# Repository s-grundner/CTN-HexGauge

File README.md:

# (EN) Hex Gauge

Customizable Automotive Gauge with CAN Bus and Integrated Inertial Measurement Unit

This is one of the initial Car Telemetry Networking (CTN) Projects.

The goal is to establish a Network of IoT devices for automotive telemtry capturing.

## Latest Revision

| Components Side | Display Side |
|-|-|
|||

## Repository Structure

- [Documentation](/documentation/)
- [Manufacturing](/manufacturing/)
- [Simulations](/simulations/)
- [Source Code](/source/)

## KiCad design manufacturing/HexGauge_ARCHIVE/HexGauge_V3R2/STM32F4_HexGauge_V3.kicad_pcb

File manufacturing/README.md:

# Revision 0

| Components Side | Display Side |
|-|-|
|||

Features:

- SD Card with SPI Mode
- IMU on I2C3 SMBA
- TFT on SPI1

# Revision 1

| Components Side | Display Side |
|-|-|
|||

Changes:

- Fullspeed SDIO Interface
- IMU on I2C1 SMBA
- Optimized Buck Converter
- Slope Control for CAN Bus
- 10pin Header for Debugging
- Larger Silkscreen
- JLC Tooling Holes

# Revision 2

| Components Side | Display Side |
|-|-|
|||

Changes:

- Simple Switcher Buckconverter Update
- Optimized Traces for
  - IMU
  - SD Card
  - SWD Interface
  - TFT Display
- Reduced Overall costs

# Revision 3

> In Development

Changes:

- [x] SD Card Dataline Pullups
- [x] change Stack-Up -> Sig/Pwr, GND, GND, Sig/Pwr
- [x] Buck converter Thinner Feedback Trace

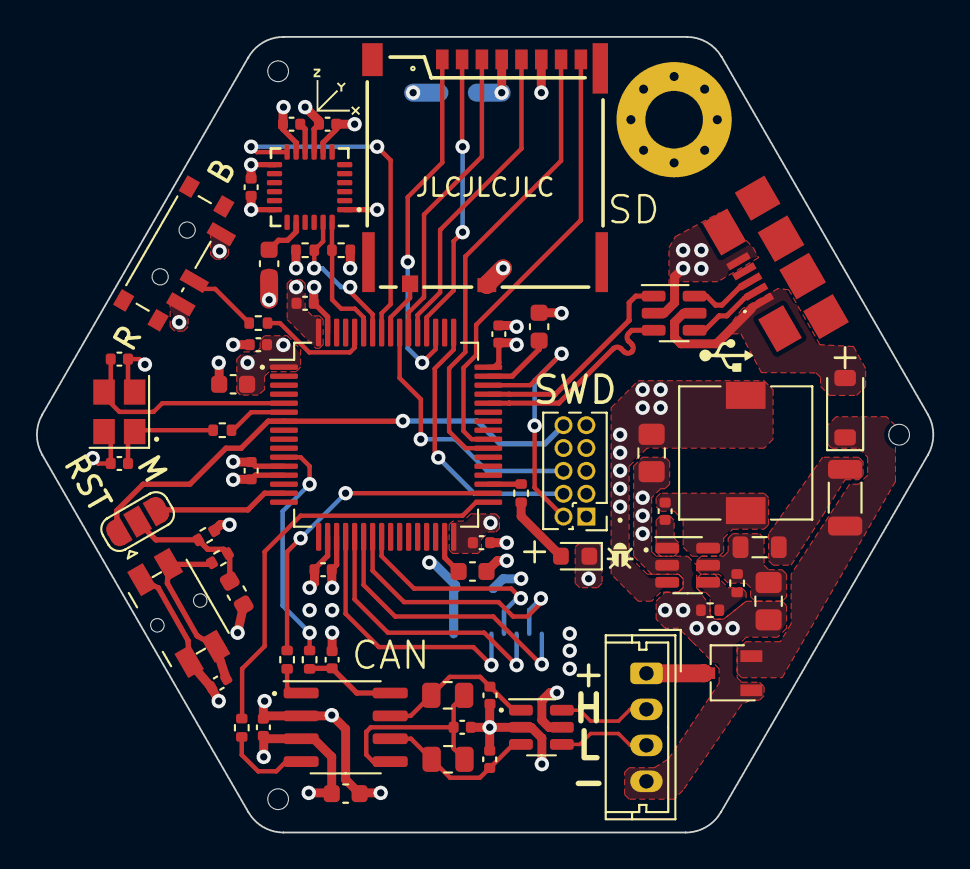
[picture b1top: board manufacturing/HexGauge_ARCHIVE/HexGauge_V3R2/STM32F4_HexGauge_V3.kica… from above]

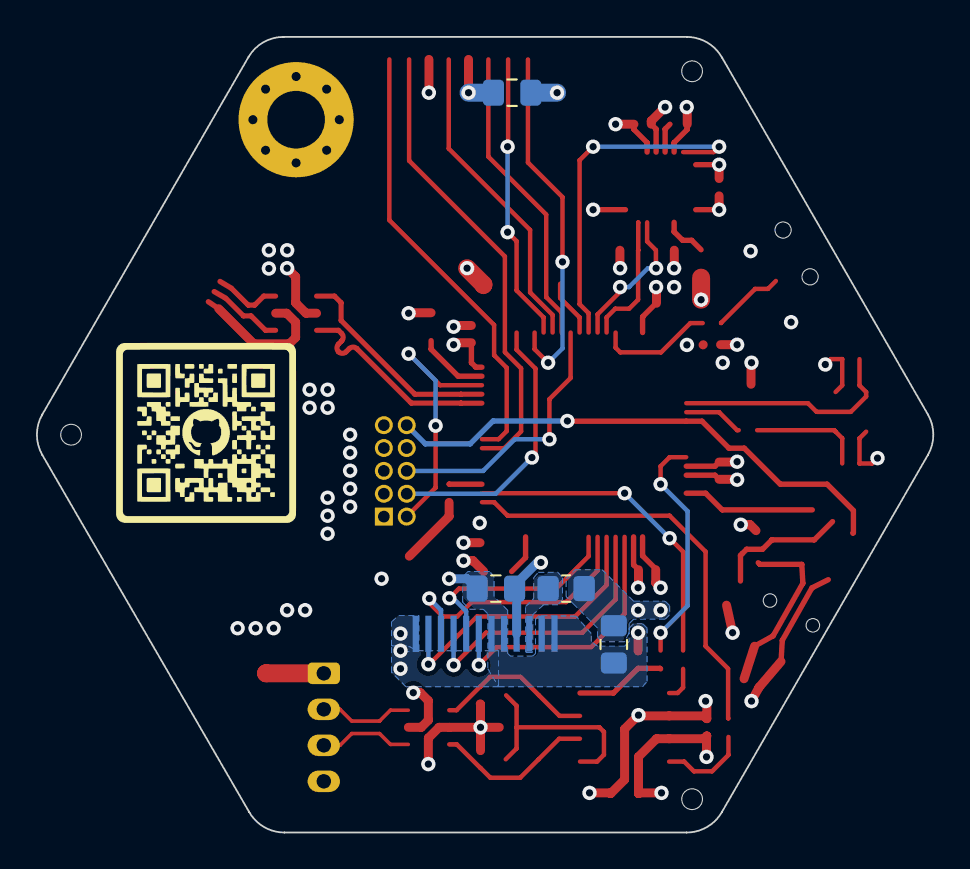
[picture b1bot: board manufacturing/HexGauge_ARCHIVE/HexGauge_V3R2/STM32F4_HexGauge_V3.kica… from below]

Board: 4 copper layers, 49.8 x 44.2 mm, 69 parts (5 on the bottom side), 59 nets.

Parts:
C1, C8, C12, C13, C17, C26: 2u2; C_0603_1608Metric
C2, C3, C4, C5, C6, C7, C9, C16, C18, C20, C21, C22, C23, C24, C25: 100n; C_0402_1005Metric
C10, C11: 12p; C_0402_1005Metric
C14, C29: 2u2; C_0805_2012Metric_Pad1.18x1.45mm_HandSolder
C15: 10u; C_0805_2012Metric_Pad1.18x1.45mm_HandSolder
C19: 10n; C_0402_1005Metric
C27, C28: 100n; C_0805_2012Metric_Pad1.18x1.45mm_HandSolder
D1: White; LED_0603_1608Metric
D2: B5819W; D_SOD-123
F1: 1A; L_1206_3216Metric
FB1: 100 @ 100MHz; L_0805_2012Metric
H1: ER_TFT128-1
H2: MountingHole; MountingHole_3.2mm_M3_Pad_Via
H3, H4, H5: JLC_Tooling
J1: USB_B_Micro; 101181920002LF
J3: Micro_SD_Card; 503398-1892
J4: Conn_01x04_Pin; Molex_Micro-Latch_53253-0470_1x04_P2.00mm_Vertical
J5: Conn_02x05_Odd_Even; PinHeader_2x05_P1.27mm_Vertical
JP1: Jumper_3_Bridged12; SolderJumper-3_P1.3mm_Open_RoundedPad1.0x1.5mm
L1: 3u3; L_7.3x7.3_H4.5
Q1: Q_PMOS_GSD; TSOT-23
R1: 10k; R_0402_1005Metric
R2, R3: 10R; R_0402_1005Metric
R4, R12, R14: 47R; R_0402_1005Metric
R5, R6, R7: 1k5; R_0402_1005Metric
R10, R16, R18: 100k; R_0402_1005Metric
R13, R15: 56R; R_0805_2012Metric
R17: 10R; R_0805_2012Metric_Pad1.20x1.40mm_HandSolder
SW1: SW_Panasonic_EVQPUC; Panasonic_EVQPUL_EVQPUC
SW2: SW_SPDT; SW_SPDT_PCM12
U1: STM32F405RGT6; LQFP-64_10x10mm_P0.5mm
U2: LMR16006YQ3; SOT-23-6
U3: SN65HVD230; SOIC-8_3.9x4.9mm_P1.27mm
U4, U6: USBLC6-2; SOT-23-6
U5: MPU-6050; InvenSense_QFN-24_4x4mm_P0.5mm
Y1: 25MHz 12pF; Crystal_SMD_3225-4Pin_3.2x2.5mm

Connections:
+3V3: C1.1, C2.1, C3.1, C4.1, C5.1, C6.1, C7.1, C15.1, C17.1, C18.1, C19.1, C20.1, C27.1, C28.1, C29.1, H1.4 (VDD), J3.4 (VDD), J5.1, L1.2, R1.1, R6.2, R7.2, R17.1, SW2.1 (A), U1.1 (VBAT), U1.13 (VDDA), U1.19 (VDD), U1.32 (VDD), U1.48 (VDD), U1.64 (VDD), U2.3 (FB), U3.3 (VCC), U4.5, U5.8 (VLOGIC), U5.13 (VDD)
+12V: J4.1, Q1.3 (D)
/Connectors/D+: J1.3 (D+), U6.6
/Connectors/D-: J1.2 (D-), U6.4
/Connectors/TFT_LEDA: H1.3 (LEDA), R17.2
/MCU/BOOT0: R2.2, U1.60 (BOOT0)
/MCU/DEBUG_LED: R5.2, U1.35 (PB14)
/MCU/HSE_IN: C10.1, U1.5 (PH0), Y1.3
/MCU/HSE_OUT: R4.2, U1.6 (PH1)
/MCU/VCAP_1: C12.1, U1.31 (VCAP_1)
/MCU/VCAP_2: C13.1, U1.47 (VCAP_2)
/MCU/XTAL_IN: C11.1, R4.1, Y1.1
/PMU/BUCK_BST: C16.1, U2.1 (CB)
/PMU/BUCK_EN: R10.2, R18.1, U2.4 (~SHDN)
/PMU/BUCK_IN: C14.1, FB1.2, R10.1, U2.5 (VIN)
/PMU/BUCK_OUT: C16.2, L1.1, U2.6 (SW)
/PMU/POST_FUSE: F1.2, FB1.1
/PMU/POST_POL: D2.1 (K), F1.1, Q1.2 (S)
/Sensors/CAN+: C21.1, R13.2, U3.7 (CANH), U4.1
/Sensors/CAN-: C23.2, R15.1, U3.6 (CANL), U4.3
/Sensors/CAN_RS: C24.1, R16.2, U3.8 (Rs)
/Sensors/VREF: C22.1, R13.1, R15.2, U3.5 (Vref)
BTN: JP1.3 (B), U1.15 (PA1)
CAN_CONN+: J4.2, U4.6
CAN_CONN-: J4.3, U4.4
CAN_RX: R14.1, U1.33 (PB12)
CAN_SC: R16.1, U1.11 (PC3)
CAN_TX: R12.1, U1.34 (PB13)
GND: C1.2, C2.2, C3.2, C4.2, C5.2, C6.2, C7.2, C8.2, C9.2, C10.2, C11.2, C12.2, C13.2, C14.2, C15.2, C17.2, C18.2, C19.2, C20.2, C21.2, C22.2, C23.1, C24.2, C25.2, C26.2, C27.2, C28.2, C29.2, D1.1 (K), H1.1 (GND), H1.2 (LEDK), H1.5 (GND), H1.6 (GND), H1.12 (GND), J1.5 (GND), J3.6 (VSS), J3.10 (SHIELD), J4.4, J5.3, J5.5, J5.9, Q1.1 (G), R18.2, SW1.1, SW2.3 (C), U1.12 (VSSA), U1.18 (VSS), U1.63 (VSS), U2.2 (GND), U3.2 (GND), U4.2, U5.1 (CLKIN), U5.9 (AD0), U5.11 (FSYNC), U5.18 (GND), U6.2, Y1.2, Y1.4
IMU_INT: U1.57 (PB5), U5.12 (INT)
IMU_SCL: R6.1, U1.58 (PB6), U5.23 (SCL)
IMU_SDA: R7.1, U1.59 (PB7), U5.24 (SDA)
NRST: J5.10, JP1.1 (A), U1.7 (NRST)
unnamed: C9.1, R3.2, SW1.2
unnamed: D1.2 (A), R5.1
unnamed: C8.1, JP1.2 (C), R1.2, R3.1
unnamed: R2.1, SW2.2 (B)
unnamed: R12.2, U3.1 (D)
unnamed: R14.2, U3.4 (R)
unnamed: C26.1, U5.20 (CPOUT)
unnamed: C25.1, U5.10 (REGOUT)
SD_CLK: J3.5 (CLK), U1.53 (PC12)
SD_CMD: J3.3 (CMD), U1.54 (PD2)
SD_DAT0: J3.7 (DAT0), U1.39 (PC8)
SD_DAT1: J3.8 (DAT1), U1.40 (PC9)
SD_DAT2: J3.1 (DAT2), U1.51 (PC10)
SD_DAT3: J3.2 (DAT3/CD), U1.52 (PC11)
SD_DET: J3.9 (DET), U1.56 (PB4)
SWCLK: J5.4, U1.49 (PA14)
SWDIO: J5.2, U1.46 (PA13)
SWO: J5.6, U1.55 (PB3)
TFT_CS: H1.8 (CS), U1.24 (PC4)
TFT_DC: H1.7 (DC), U1.20 (PA4)
TFT_MOSI: H1.10 (MOSI), U1.23 (PA7)
TFT_RST: H1.11 (RST), U1.22 (PA6)
TFT_SCK: H1.9 (SCK), U1.21 (PA5)
USB_D+: U1.45 (PA12), U6.1
USB_D-: U1.44 (PA11), U6.3
VBUS: D2.2 (A), J1.1 (VBUS), U6.5

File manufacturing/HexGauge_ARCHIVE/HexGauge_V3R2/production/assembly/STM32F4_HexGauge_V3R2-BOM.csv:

Comment,Designator,Footprint,LCSC
2u2,"C1, C8, C12, C13, C17, C26",Capacitor_SMD:C_0603_1608Metric,C23630
100n,"C2, C3, C4, C5, C6, C7, C9, C16, C18, C20, C21, C22, C23, C24, C25",Capacitor_SMD:C_0402_1005Metric,C1525
12p,"C10, C11",Capacitor_SMD:C_0402_1005Metric,C1547
10n,C19,Capacitor_SMD:C_0402_1005Metric,C15195
White,D1,LED_SMD:LED_0603_1608Metric,C2290
B5819W,D2,Diode_SMD:D_SOD-123,C8598
1A,F1,Inductor_SMD:L_1206_3216Metric,C209741
100 @ 100MHz,FB1,Inductor_SMD:L_0805_2012Metric,C1015
USB_B_Micro,J1,SamacSys_Parts:101181920002LF,C397452
Micro_SD_Card,J3,SamacSys_Parts:503398-1892,C428492
Q_PMOS_GSD,Q1,Package_TO_SOT_SMD:TSOT-23,C15127
10k,R1,Resistor_SMD:R_0402_1005Metric,C25744
10R,"R2, R3",Resistor_SMD:R_0402_1005Metric,C25077
47R,"R4, R12, R14",Resistor_SMD:R_0402_1005Metric,C25118
1k5,"R5, R6, R7",Resistor_SMD:R_0402_1005Metric,C25867
100k,"R10, R16, R18",Resistor_SMD:R_0402_1005Metric,C25741
56R,"R13, R15",Resistor_SMD:R_0805_2012Metric,C17757
SW_Panasonic_EVQPUC,SW1,Button_Switch_SMD:Panasonic_EVQPUL_EVQPUC,C79174
SW_SPDT,SW2,Button_Switch_SMD:SW_SPDT_PCM12,C221841
STM32F405RGT6,U1,Package_QFP:LQFP-64_10x10mm_P0.5mm,C15742
SN65HVD230,U3,Package_SO:SOIC-8_3.9x4.9mm_P1.27mm,C12084
USBLC6-2,"U4, U6",Package_TO_SOT_SMD:SOT-23-6,C7519
MPU-6050,U5,Sensor_Motion:InvenSense_QFN-24_4x4mm_P0.5mm,C24112
25MHz 12pF,Y1,Crystal:Crystal_SMD_3225-4Pin_3.2x2.5mm,C9006

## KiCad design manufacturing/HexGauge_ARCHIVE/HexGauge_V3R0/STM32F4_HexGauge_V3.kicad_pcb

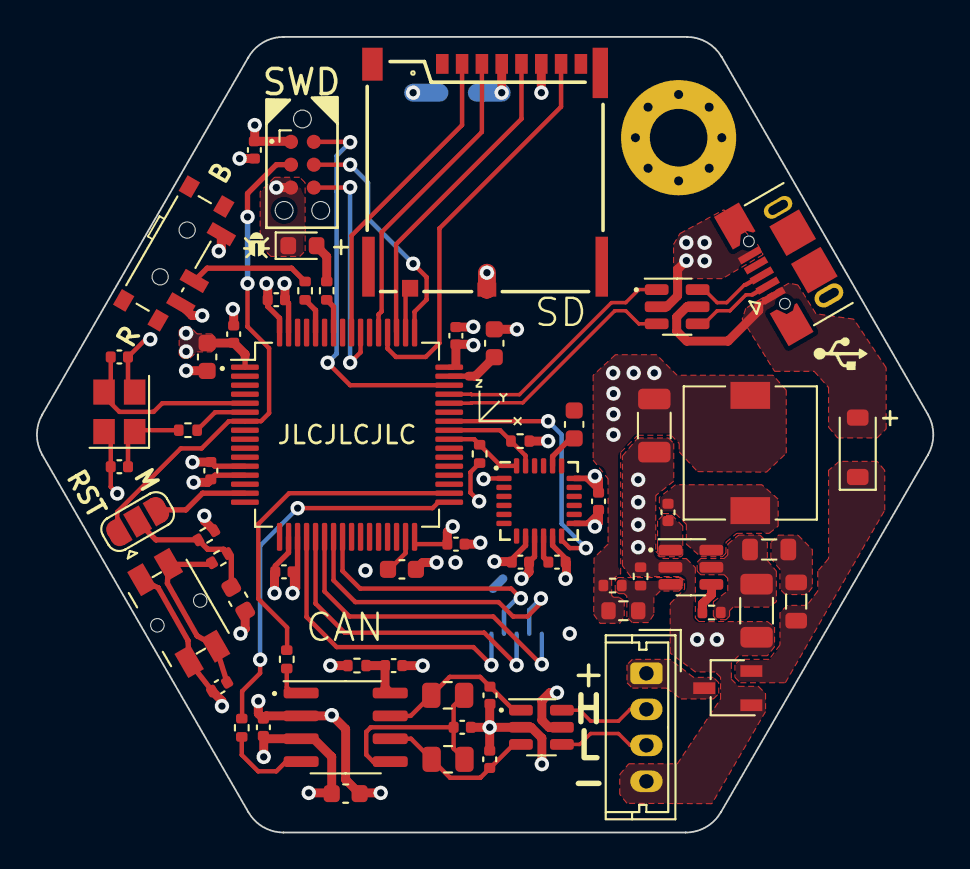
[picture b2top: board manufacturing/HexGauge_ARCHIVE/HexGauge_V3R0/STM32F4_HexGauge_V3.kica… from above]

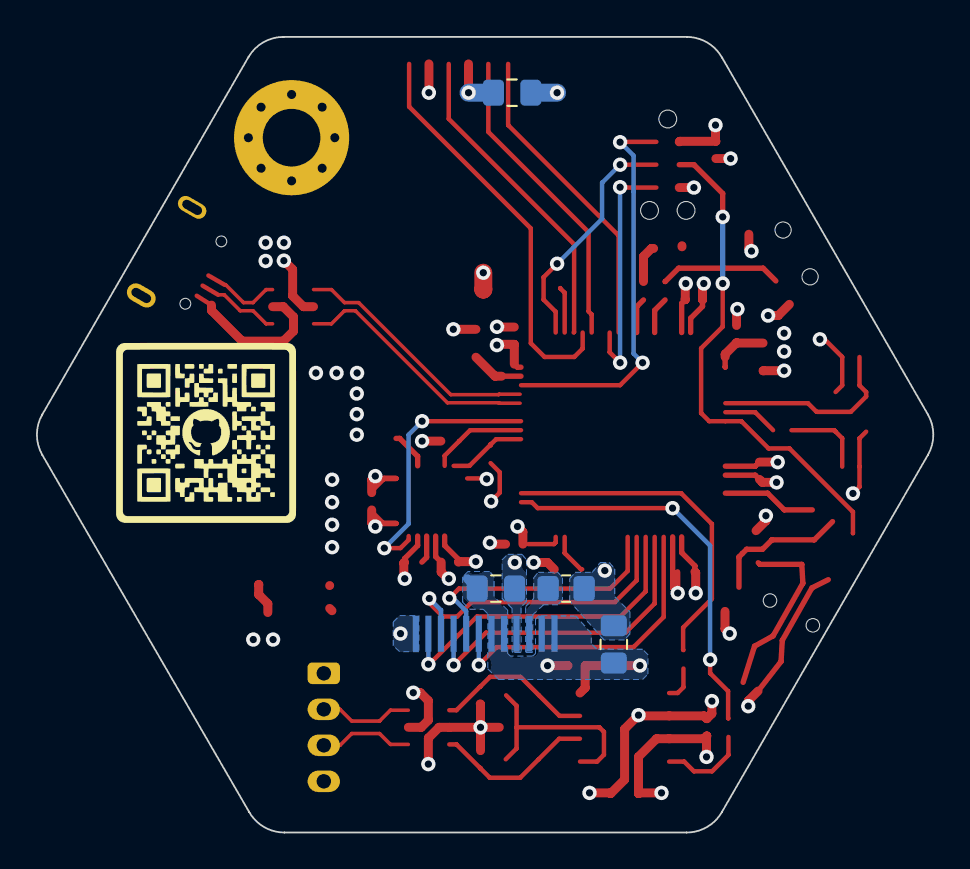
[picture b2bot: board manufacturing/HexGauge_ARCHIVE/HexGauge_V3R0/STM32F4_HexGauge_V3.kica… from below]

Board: 4 copper layers, 49.8 x 44.2 mm, 69 parts (5 on the bottom side), 57 nets.

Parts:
C1, C9, C10, C15, C24, C27: 2u2; C_0603_1608Metric
C2, C3, C4, C5, C6, C16, C18, C19, C20, C21, C22, C23, C28, C29: 100n; C_0402_1005Metric
C7, C8: 12p; C_0402_1005Metric
C11: 22n; C_0402_1005Metric
C12: 470n; C_0402_1005Metric
C13, C14: 47u; C_1206_3216Metric
C17: 10n; C_0402_1005Metric
C25, C30: 100n; C_0805_2012Metric_Pad1.18x1.45mm_HandSolder
C26: 2u2; C_0805_2012Metric_Pad1.18x1.45mm_HandSolder
D1: B5819W; D_SOD-123
D2: White; LED_0603_1608Metric
F1: 1A; L_0805_2012Metric
FB1: 100 @ 100MHz; L_0805_2012Metric
H1: ER_TFT128-1
H2: MountingHole; MountingHole_3.2mm_M3_Pad_Via
J1: USB_B_Micro; USB_Micro-B_XKB_U254-051T-4BH83-F1S
J2: Conn_ARM_SWD_TC2030-NL; Tag-Connect_TC2030-IDC-NL_2x03_P1.27mm_Vertical
J3: Micro_SD_Card; 503398-1892
J4: Conn_01x04_Pin; Molex_Micro-Latch_53253-0470_1x04_P2.00mm_Vertical
JP1: Jumper_3_Bridged12; SolderJumper-3_P1.3mm_Open_RoundedPad1.0x1.5mm
L1: 4u7; L_7.3x7.3_H4.5
Q1: Q_PMOS_GSD; TSOT-23
R1, R17: 10R; R_0402_1005Metric
R2, R10, R12: 47R; R_0402_1005Metric
R3, R4, R9, R14: 1k5; R_0402_1005Metric
R5: 33k; R_0402_1005Metric
R6: 560k; R_0603_1608Metric
R7: 100k; R_0402_1005Metric
R8, R16: 10k; R_0402_1005Metric
R11, R13: 56R; R_0805_2012Metric
R15: 10R; R_0805_2012Metric_Pad1.20x1.40mm_HandSolder
SW1: SW_SPDT; SW_SPDT_PCM12
SW2: SW_Omron_B3FS; Panasonic_EVQPUL_EVQPUC
U1: STM32F405RGT6; LQFP-64_10x10mm_P0.5mm
U2: TPMP2359D; TSOT-23-6
U3: SN65HVD230; SOIC-8_3.9x4.9mm_P1.27mm
U4: USBLC6-2; SOT-23-6
U5: MPU-6050; InvenSense_QFN-24_4x4mm_P0.5mm
U6: USBLC6-4; SOT-23-6
Y1: 25MHz 12pF; Crystal_SMD_3225-4Pin_3.2x2.5mm

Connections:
+3V3: C1.1, C2.1, C3.1, C4.1, C5.1, C6.1, C12.1, C13.1, C15.1, C16.1, C17.1, C18.1, C25.1, C26.1, C29.1, C30.1, H1.4 (VDD), J2.1 (VCC), J3.4 (VDD), L1.2, R3.2, R4.2, R5.1, R6.1, R15.1, R16.1, SW1.1 (A), U1.1 (VBAT), U1.13 (VDDA), U1.19 (VDD), U1.32 (VDD), U1.48 (VDD), U1.64 (VDD), U3.3 (VCC), U4.5, U5.8 (VLOGIC), U5.13 (VDD)
+12V: J4.1, Q1.3 (D)
/Connectors/D+: J1.3 (D+), U6.6
/Connectors/D-: J1.2 (D-), U6.4
/Connectors/TFT_LEDA: H1.3 (LEDA), R15.2
/MCU/BOOT0: R1.2, U1.60 (BOOT0)
/MCU/DEBUG_LED: R9.2, U1.58 (PB6)
/MCU/HSE_IN: C7.1, U1.5 (PH0), Y1.3
/MCU/HSE_OUT: R2.2, U1.6 (PH1)
/MCU/VCAP_1: C9.1, U1.31 (VCAP_1)
/MCU/VCAP_2: C10.1, U1.47 (VCAP_2)
/MCU/XTAL_IN: C8.1, R2.1, Y1.1
/PMU/BUCK_BST: C11.1, U2.1 (BST)
/PMU/BUCK_EN: R7.2, U2.4 (EN)
/PMU/BUCK_FB: R5.2, R6.2, R8.1, U2.3 (FB)
/PMU/BUCK_IN: C14.1, FB1.2, R7.1, U2.5 (IN)
/PMU/BUCK_OUT: C11.2, L1.1, U2.6 (SW)
/PMU/POST_FUSE: F1.2, FB1.1
/PMU/POST_POL: D1.1 (K), F1.1, Q1.2 (S)
/Sensors/CAN+: C19.1, R11.2, U3.7 (CANH), U4.1
/Sensors/CAN-: C21.2, R13.1, U3.6 (CANL), U4.3
/Sensors/CAN_RS: C22.1, R14.2, U3.8 (Rs)
/Sensors/VREF: C20.1, R11.1, R13.2, U3.5 (Vref)
BTN: JP1.3 (B), U1.15 (PA1)
CAN_CONN+: J4.2, U4.6
CAN_CONN-: J4.3, U4.4
CAN_RX: R12.1, U1.33 (PB12)
CAN_TX: R10.1, U1.34 (PB13)
GND: C1.2, C2.2, C3.2, C4.2, C5.2, C6.2, C7.2, C8.2, C9.2, C10.2, C12.2, C13.2, C14.2, C15.2, C16.2, C17.2, C18.2, C19.2, C20.2, C21.1, C22.2, C23.2, C24.2, C25.2, C26.2, C27.2, C28.2, C29.2, C30.2, D2.1 (K), H1.1 (GND), H1.2 (LEDK), H1.5 (GND), H1.6 (GND), H1.12 (GND), J1.5 (GND), J2.5 (GND), J3.6 (VSS), J3.10 (SHIELD), J4.4, Q1.1 (G), R8.2, R14.1, SW1.3 (C), SW2.1, U1.12 (VSSA), U1.18 (VSS), U1.63 (VSS), U2.2 (GND), U3.2 (GND), U4.2, U5.1 (CLKIN), U5.9 (AD0), U5.11 (FSYNC), U5.18 (GND), U6.2, Y1.2, Y1.4
IMU_INT: U1.42 (PA9), U5.12 (INT)
IMU_SCL: R3.1, U1.41 (PA8), U5.23 (SCL)
IMU_SDA: R4.1, U1.40 (PC9), U5.24 (SDA)
NRST: J2.3 (~RESET), JP1.1 (A), U1.7 (NRST)
unnamed: C28.1, R17.2, SW2.2
unnamed: D2.2 (A), R9.1
unnamed: C27.1, JP1.2 (C), R16.2, R17.1
unnamed: R1.1, SW1.2 (B)
unnamed: R10.2, U3.1 (D)
unnamed: R12.2, U3.4 (R)
unnamed: C24.1, U5.20 (CPOUT)
unnamed: C23.1, U5.10 (REGOUT)
SD_CLK: J3.5 (CLK), U1.51 (PC10)
SD_CMD: J3.3 (CMD), U1.53 (PC12)
SD_DAT0: J3.7 (DAT0), U1.52 (PC11)
SD_DAT3: J3.2 (DAT3/CD), U1.56 (PB4)
SD_DET: J3.9 (DET), U1.50 (PA15)
SWCLK: J2.4 (SWCLK), U1.49 (PA14)
SWDIO: J2.2 (SWDIO), U1.46 (PA13)
SWO: J2.6 (SWO), U1.55 (PB3)
TFT_CS: H1.8 (CS), U1.24 (PC4)
TFT_DC: H1.7 (DC), U1.20 (PA4)
TFT_MOSI: H1.10 (MOSI), U1.23 (PA7)
TFT_RST: H1.11 (RST), U1.22 (PA6)
TFT_SCK: H1.9 (SCK), U1.21 (PA5)
USB_D+: U1.45 (PA12), U6.1
USB_D-: U1.44 (PA11), U6.3
VBUS: D1.2 (A), J1.1 (VBUS), U6.5

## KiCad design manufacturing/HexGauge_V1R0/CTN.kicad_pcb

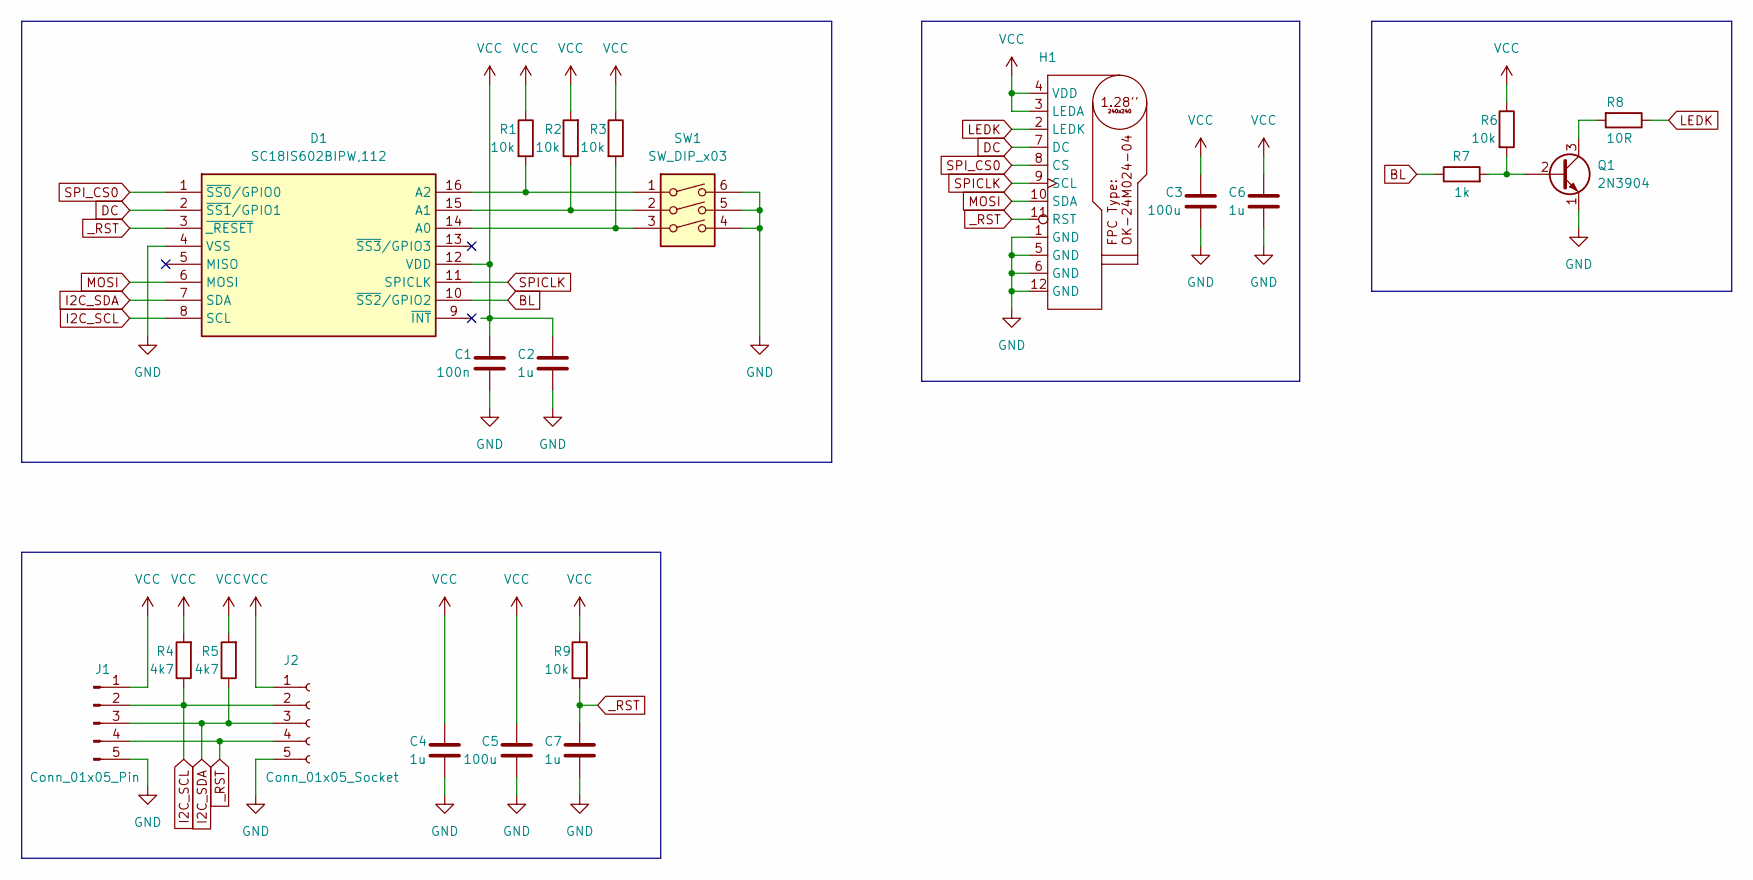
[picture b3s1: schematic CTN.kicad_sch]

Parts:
C1: 100n; C_0805_2012Metric
C2, C4, C6, C7: 1u; C_0805_2012Metric
C3, C5: 100u; C_0805_2012Metric
D1: SC18IS602BIPW,112; SOP65P640X110-16N; Manufacturer_Part_Number SC18IS602BIPW,112
H1: ER_TFT128-2
J1: Conn_01x05_Pin; PinHeader_1x05_P2.54mm_Horizontal
J2: Conn_01x05_Socket; PinSocket_1x05_P2.54mm_Horizontal
Q1: 2N3904; SOT-23
R1, R2, R3, R6, R9: 10k; R_0805_2012Metric_Pad1.20x1.40mm_HandSolder
R4, R5: 4k7; R_0805_2012Metric_Pad1.20x1.40mm_HandSolder
R7: 1k; R_0805_2012Metric_Pad1.20x1.40mm_HandSolder
R8: 10R; R_0805_2012Metric_Pad1.20x1.40mm_HandSolder
SW1: SW_DIP_x03; SW_DIP_SPSTx03_Slide_Omron_A6S-310x_W8.9mm_P2.54mm

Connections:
BL: D1.10 (~SS2/GPIO2), R7.1
DC: D1.2 (~SS1/GPIO1), H1.7 (DC)
GND: C1.2, C2.2, C3.2, C4.2, C5.2, C6.2, C7.2, D1.4 (VSS), H1.1 (GND), H1.5 (GND), H1.6 (GND), H1.12 (GND), J1.5, J2.5, Q1.1 (E), SW1.4, SW1.5, SW1.6
I2C_SCL: D1.8 (SCL), J1.2, J2.2, R4.1
I2C_SDA: D1.7 (SDA), J1.3, J2.3, R5.1
LEDK: H1.2 (LEDK), R8.1
MOSI: D1.6 (MOSI), H1.10 (SDA)
unnamed: D1.14 (A0), R3.2, SW1.3
unnamed: D1.15 (A1), R2.1, SW1.2
unnamed: D1.16 (A2), R1.2, SW1.1
unnamed: Q1.2 (B), R6.2, R7.2
unnamed: Q1.3 (C), R8.2
SPICLK: D1.11 (SPICLK), H1.9 (SCL)
SPI_CS0: D1.1 (~SS0/GPIO0), H1.8 (CS)
VCC: C1.1, C2.1, C3.1, C4.1, C5.1, C6.1, D1.12 (VDD), H1.3 (LEDA), H1.4 (VDD), J1.1, J2.1, R1.1, R2.2, R3.1, R4.2, R5.2, R6.1, R9.1
_RST: C7.1, D1.3 (~_RESET), H1.11 (RST), J1.4, J2.4, R9.2

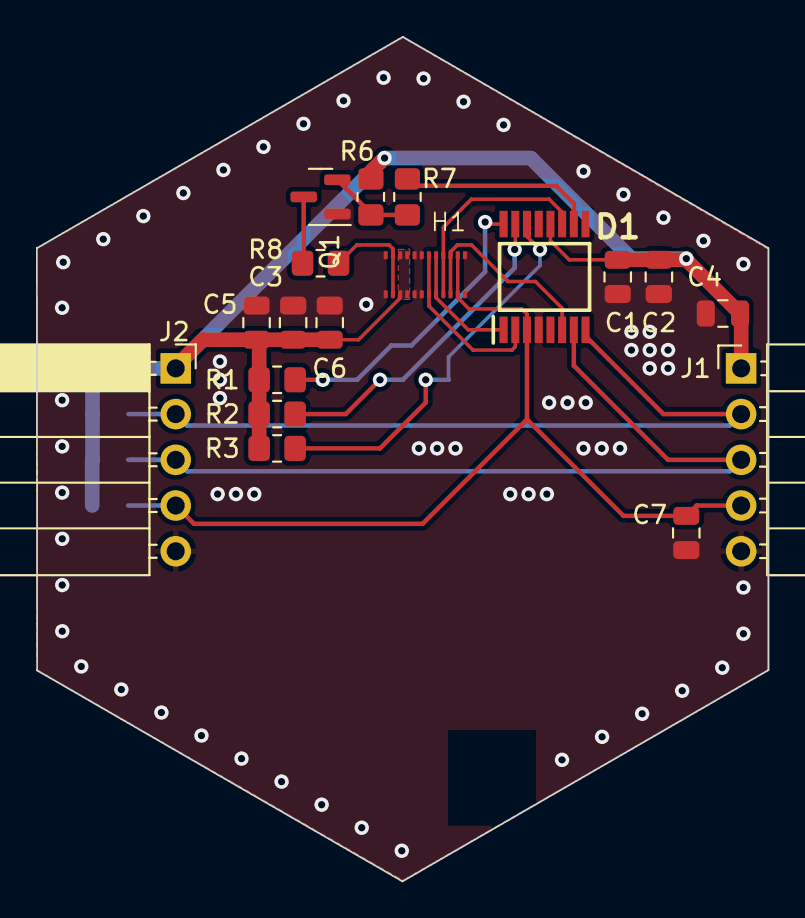
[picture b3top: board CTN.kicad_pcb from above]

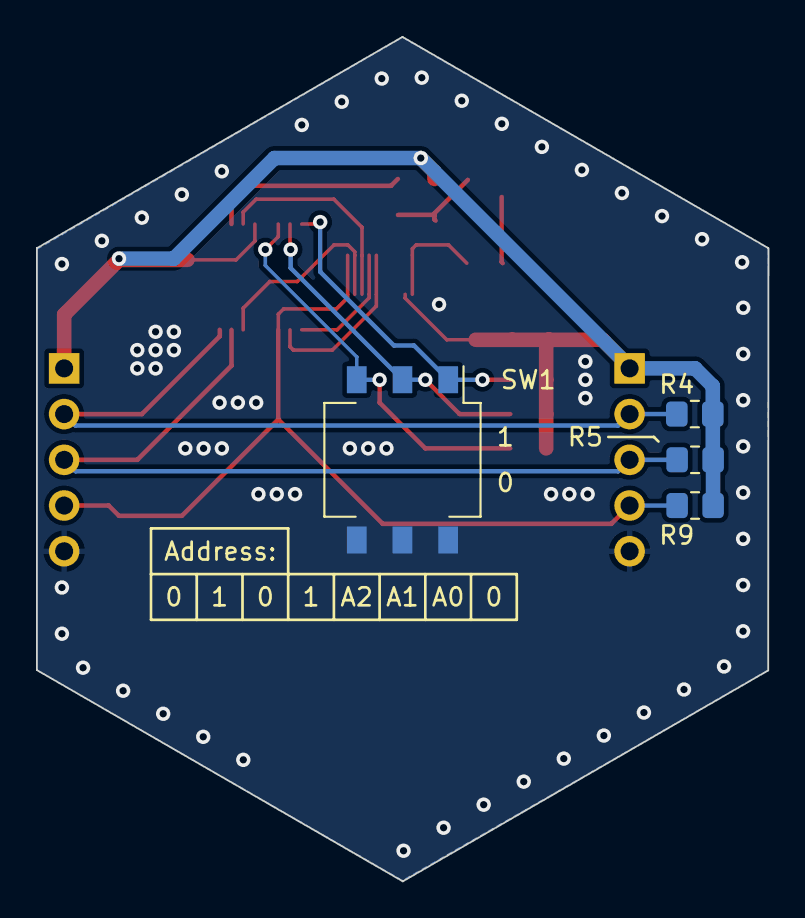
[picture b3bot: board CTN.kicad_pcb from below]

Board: 2 copper layers, 40.6 x 46.9 mm, 22 parts (4 on the bottom side), 16 nets.

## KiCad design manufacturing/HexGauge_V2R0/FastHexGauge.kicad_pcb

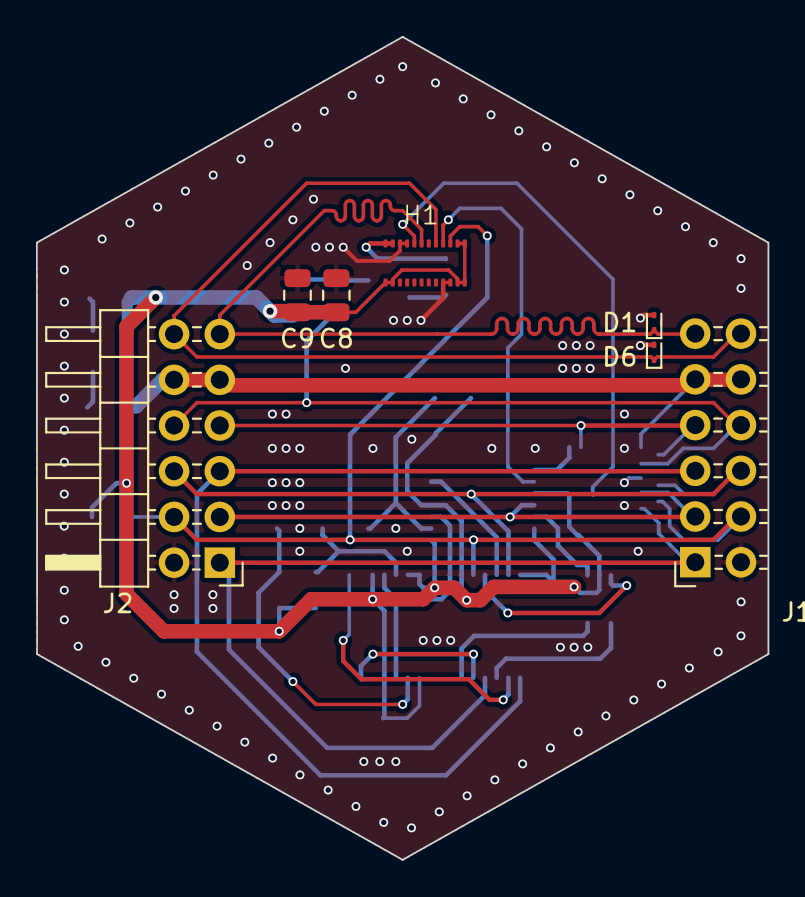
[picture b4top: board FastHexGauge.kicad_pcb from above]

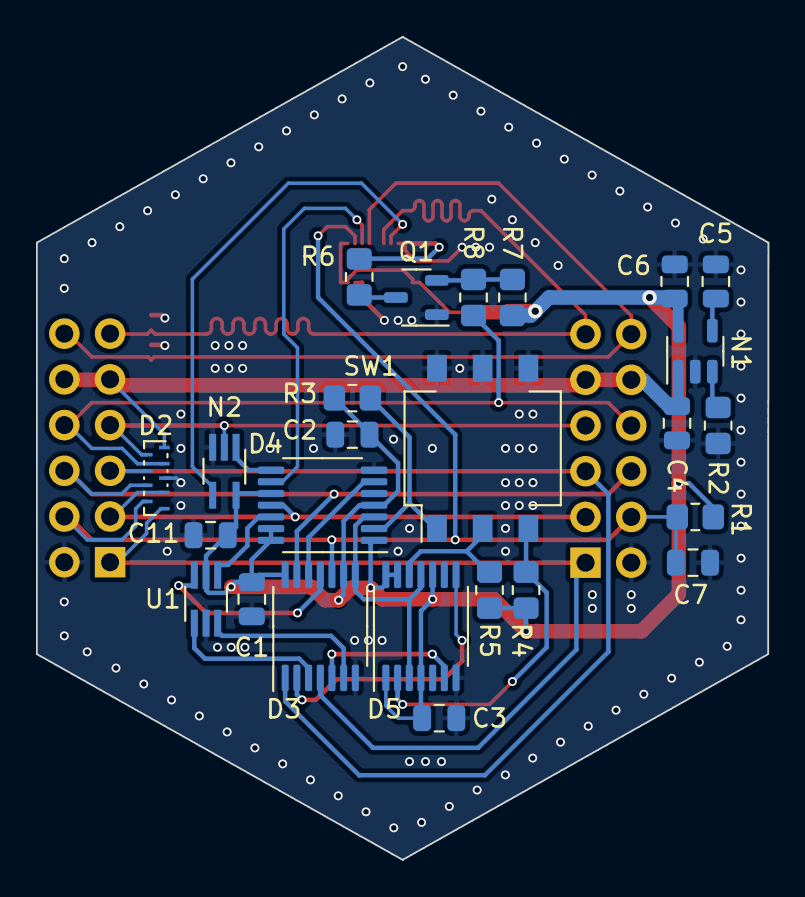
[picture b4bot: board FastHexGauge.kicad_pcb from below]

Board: 2 copper layers, 40.6 x 45.7 mm, 32 parts (25 on the bottom side), 31 nets.

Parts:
C1, C2, C3: 100n; C_0805_2012Metric
C4, C8: 100u; C_0805_2012Metric
C5: 22n; C_0805_2012Metric
C6, C7, C9: 1u; C_0805_2012Metric
C11: 220n; C_0805_2012Metric
D1, D6: ESD7351XV2T1G; D_SOD-923
D2: DT1240A-08LP3810; UDFN-9_1.0x3.8mm_P0.5mm
D3: 74LVC86; TSSOP-14_4.4x5mm_P0.65mm
D4, D5: 74LVC74; TSSOP-14_4.4x5mm_P0.65mm
H1: ER_TFT128-2
J1: Conn_02x06_Counter_Clockwise; PinSocket_2x06_P2.54mm_Horizontal
J2: Conn_02x06_Counter_Clockwise; PinHeader_2x06_P2.54mm_Horizontal
N1: RT9193-33; SOT-23-5
N2: 74LVC1G126; SOT-353_SC-70-5_Handsoldering
Q1: 2N3904; SOT-23-3
R1, R2, R3, R4, R5, R7: 10k; R_0805_2012Metric_Pad1.20x1.40mm_HandSolder
R6: 10R; R_0805_2012Metric_Pad1.20x1.40mm_HandSolder
R8: 1k; R_0805_2012Metric_Pad1.20x1.40mm_HandSolder
SW1: SW_DIP_x03; SW_DIP_SPSTx03_Slide_Omron_A6S-310x_W8.9mm_P2.54mm
U1: 74LVC1G10; SOT-363_SC-70-6_Handsoldering

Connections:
+3V3: C4.1, D2.5 (K4), J1.9, J1.10, J2.9, J2.10, N1.1 (VIN)
BL_BUS: D2.4 (K3), J1.8, J2.8, R8.1
CS0: D2.8 (K7), D3.13, J1.6, J2.6
CS1: D2.7 (K6), D3.1, J1.5, J2.5
CS2: D2.1 (K1), D3.4, J1.1, J2.1
DC: H1.5 (DC), N2.4
DC_BUS: D2.6 (K5), J1.7, J2.7, N2.2
GND: C1.2, C2.2, C3.2, C4.2, C5.2, C6.2, C7.2, C8.2, C9.2, C11.2, D1.2 (A2), D2.3 (A), D3.7 (GND), D4.7 (GND), D5.7 (GND), D6.2 (A2), H1.3 (GND), H1.4 (GND), H1.15 (GND), H1.16 (GND), J1.2, J2.2, N1.2 (GND), N2.3 (GND), Q1.1 (E), R2.2, SW1.4, SW1.5, SW1.6, U1.2 (GND)
LEDK: H1.1 (LEDK1), H1.2 (LEDK2), R6.1
MOSI_BUS: D1.1 (A1), H1.6 (MOSI), J1.11, J2.11
unnamed: D3.3, U1.1
unnamed: D3.6, U1.3
unnamed: D3.11, U1.6
unnamed: D3.8, D4.3 (C), D5.3 (C), D5.11 (C)
unnamed: D4.2 (D), R3.2, SW1.1
unnamed: D3.12, D4.6 (~Q)
unnamed: D4.12 (D), U1.4
unnamed: D4.8 (~Q), N2.1
unnamed: D5.2 (D), R5.2, SW1.3
unnamed: D3.5, D5.6 (~Q)
unnamed: D5.12 (D), R4.1, SW1.2
unnamed: D3.2, D5.8 (~Q)
unnamed: C5.1, N1.4 (BYP)
unnamed: N1.3 (EN), R2.1
unnamed: Q1.2 (B), R7.2, R8.2
unnamed: Q1.3 (C), R6.2
SCL_BUS: D6.1 (A1), H1.8 (SCL), J1.12, J2.12
SYN_BUS: D2.2 (K2), D4.11 (C), J1.3, J2.3
VCC: C1.1, C2.1, C3.1, C6.1, C8.1, C9.1, C11.1, D3.9, D3.14 (VCC), D4.1 (~R), D4.4 (~S), D4.10 (~S), D4.13 (~R), D4.14 (VCC), D5.1 (~R), D5.4 (~S), D5.10 (~S), D5.13 (~R), D5.14 (VCC), H1.11 (VDDIO), H1.12 (VDDIO), H1.13 (VDD), H1.14 (VDD), H1.23 (LEDA2), H1.24 (LEDA1), N1.5 (VOUT), N2.5 (VCC), R1.1, R3.1, R4.2, R5.1, R7.1, U1.5 (VCC)
_CS: D4.9 (Q), H1.9 (CS)
_RST_BUS: C7.1, D2.9 (K8), D3.10, H1.10 (RST), J1.4, J2.4, R1.2

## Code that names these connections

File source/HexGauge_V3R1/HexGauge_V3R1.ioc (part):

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Mcu.Name=STM32F405RGTx
Mcu.Package=LQFP64
Mcu.UserName=STM32F405RGTx
PA1.GPIOParameters=GPIO_PuPd,GPIO_Label
PA1.GPIO_Label=BTN_INT
PA1.GPIO_PuPd=GPIO_PULLUP
PA1.Signal=GPXTI1
PA11.Mode=Device_Only
PA11.Signal=USB_OTG_FS_DM
PA12.Mode=Device_Only
PA12.Signal=USB_OTG_FS_DP
PA13.Mode=Trace_Asynchronous_SW
PA13.Signal=SYS_JTMS-SWDIO
PA14.Mode=Trace_Asynchronous_SW
PA14.Signal=SYS_JTCK-SWCLK
PA15.GPIOParameters=GPIO_PuPd,GPIO_Label,GPIO_Mode
PA15.GPIO_Label=SDIO_DET
PA15.GPIO_Mode=GPIO_MODE_INPUT
PA15.GPIO_PuPd=GPIO_PULLUP
PA15.Signal=GPIO_Input
PA4.GPIOParameters=GPIO_Speed,GPIO_Label
PA4.GPIO_Label=TFT_DC
PA4.GPIO_Speed=GPIO_SPEED_FREQ_VERY_HIGH
PA4.Signal=GPIO_Output
PA5.Mode=TX_Only_Simplex_Unidirect_Master
PA5.Signal=SPI1_SCK
PA6.GPIOParameters=PinState,GPIO_PuPd,GPIO_Label
PA6.GPIO_Label=TFT_NRST
PA6.GPIO_PuPd=GPIO_PULLUP
PA6.PinState=GPIO_PIN_SET
PA6.Signal=GPIO_Output
PA7.Mode=TX_Only_Simplex_Unidirect_Master
PA7.Signal=SPI1_MOSI
PB12.Mode=CAN_Activate
PB12.Signal=CAN2_RX
PB13.Mode=CAN_Activate
PB13.Signal=CAN2_TX
PB3.Mode=Trace_Asynchronous_SW
PB3.Signal=SYS_JTDO-SWO
PB5.Mode=SMBus-Alert-mode
PB5.Signal=I2C1_SMBA
PB6.Mode=SMBus-Alert-mode
PB6.Signal=I2C1_SCL
PB7.Mode=SMBus-Alert-mode
PB7.Signal=I2C1_SDA
PC10.Mode=SD_4_bits_Wide_bus
PC10.Signal=SDIO_D2
PC11.Mode=SD_4_bits_Wide_bus
PC11.Signal=SDIO_D3
PC12.Mode=SD_4_bits_Wide_bus
PC12.Signal=SDIO_CK
PC3.GPIOParameters=GPIO_Label
PC3.GPIO_Label=CAN2_SLOPECTRL
PC3.Signal=GPIO_Output
PC4.GPIOParameters=GPIO_Speed,PinState,GPIO_PuPd,GPIO_Label
PC4.GPIO_Label=TFT_NCS
PC4.GPIO_PuPd=GPIO_PULLUP
PC4.GPIO_Speed=GPIO_SPEED_FREQ_VERY_HIGH
PC4.PinState=GPIO_PIN_SET
PC4.Signal=GPIO_Output
PC8.Mode=SD_4_bits_Wide_bus
PC8.Signal=SDIO_D0
PC9.Mode=SD_4_bits_Wide_bus
PC9.Signal=SDIO_D1
PD2.Mode=SD_4_bits_Wide_bus
PD2.Signal=SDIO_CMD
PH0-OSC_IN.Mode=HSE-External-Oscillator
PH0-OSC_IN.Signal=RCC_OSC_IN
PH1-OSC_OUT.Mode=HSE-External-Oscillator
PH1-OSC_OUT.Signal=RCC_OSC_OUT
RCC.HSE_VALUE=25000000
RCC.SYSCLKFreq_VALUE=168000000
RCC.SYSCLKSource=RCC_SYSCLKSOURCE_PLLCLK
board=custom

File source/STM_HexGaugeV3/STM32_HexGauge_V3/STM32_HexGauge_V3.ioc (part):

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Mcu.Name=STM32F405RGTx
Mcu.Package=LQFP64
Mcu.UserName=STM32F405RGTx
PA11.Mode=Device_Only
PA11.Signal=USB_OTG_FS_DM
PA12.Mode=Device_Only
PA12.Signal=USB_OTG_FS_DP
PA13.Mode=Trace_Asynchronous_SW
PA13.Signal=SYS_JTMS-SWDIO
PA14.Mode=Trace_Asynchronous_SW
PA14.Signal=SYS_JTCK-SWCLK
PA15.GPIOParameters=GPIO_Label
PA15.GPIO_Label=SPI3_SD_CS
PA15.Signal=GPIO_Output
PA3.GPIOParameters=GPIO_Label
PA3.GPIO_Label=BTN_INT
PA3.Signal=GPXTI3
PA4.GPIOParameters=GPIO_Label
PA4.GPIO_Label=SPI1_TFT_RST
PA4.Signal=GPIO_Output
PA5.GPIOParameters=GPIO_Label
PA5.GPIO_Label=SPI1_TFT_SCK
PA5.Mode=TX_Only_Simplex_Unidirect_Master
PA5.Signal=SPI1_SCK
PA6.GPIOParameters=GPIO_Label
PA6.GPIO_Label=SPI1_TFT_CS
PA6.Signal=GPIO_Output
PA7.GPIOParameters=GPIO_Label
PA7.GPIO_Label=SPI1_TFT_MOSI
PA7.Mode=TX_Only_Simplex_Unidirect_Master
PA7.Signal=SPI1_MOSI
PA8.GPIOParameters=GPIO_Label
PA8.GPIO_Label=I2C3__IMU_SCL
PA8.Mode=SMBus-Alert-mode
PA8.Signal=I2C3_SCL
PA9.Mode=SMBus-Alert-mode
PA9.Signal=I2C3_SMBA
PB12.Mode=CAN_Activate
PB12.Signal=CAN2_RX
PB13.Mode=CAN_Activate
PB13.Signal=CAN2_TX
PB3.Mode=Trace_Asynchronous_SW
PB3.Signal=SYS_JTDO-SWO
PC10.GPIOParameters=GPIO_Label
PC10.GPIO_Label=SPI3_SD_SCK
PC10.Mode=Full_Duplex_Master
PC10.Signal=SPI3_SCK
PC11.GPIOParameters=GPIO_Label
PC11.GPIO_Label=SPI3_SD_MISO
PC11.Mode=Full_Duplex_Master
PC11.Signal=SPI3_MISO
PC12.GPIOParameters=GPIO_Label
PC12.GPIO_Label=SPI3_SD_MOSI
PC12.Mode=Full_Duplex_Master
PC12.Signal=SPI3_MOSI
PC4.GPIOParameters=GPIO_Label
PC4.GPIO_Label=SPI1_TFT_DC
PC4.Signal=GPIO_Output
PC9.GPIOParameters=GPIO_Label
PC9.GPIO_Label=I2C3_IMU_SDA
PC9.Mode=SMBus-Alert-mode
PC9.Signal=I2C3_SDA
PH0-OSC_IN.Mode=HSE-External-Oscillator
PH0-OSC_IN.Signal=RCC_OSC_IN
PH1-OSC_OUT.Mode=HSE-External-Oscillator
PH1-OSC_OUT.Signal=RCC_OSC_OUT
RCC.HSE_VALUE=24000000
RCC.SYSCLKFreq_VALUE=16000000
board=custom

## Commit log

2023-07-24 README
2023-07-30 update README and project planning
2023-07-30 Added Prototype Daughterboard Version 1
    with simple I2C to SPI conversion chip.
    SPI clock max 1.7MHz which is to slow to drive TFT displays:
    $\dfrac{250px \cdot 250px \cdot 16\frac{bit}{px}}{1.7 \cdot 10^{6}Hz}=0.588s = 1.7Hz$
    not including I2C Overhead
2023-07-30 Added Prototype Daughterboard Version 2
    # Description
    SPI Chipselect Decoder with selectable CS Code
    Selected Logicfamily is LVC with very low $t_{pd}$ (few $ns$)
    CS Code selectable with 3 pol dip switch (latched on reset to avoid codebouncing)
    3 to 8 Demux + 8 to 1 Code selector combination not available in LVC.
    - Custom EXOR decoder with $t_{pd}$ of about 1 clock cycle on max SPI freq ($80MHz$)
2023-07-30 started Controller Motherboard
2023-08-03 Updated Board to version 3
2023-08-03 Updated Board
    Added Mounting Hole and 3D Packages
2023-08-05 Updated Board and added Images
2023-08-05 Added Source Code Libraries
2023-08-06 Updated Board do Revision 3
    SDIO Interface takes up I2C3 pin from the IMU.
    The IMU had to be configured to I2C1.
    SWD Connector position swapped with IMU on Layout
    Source has to be regenerated
2023-08-06 added old board
2023-08-06 V3R0 SPI SD Card Update
2023-08-06 added new source
    Configured workspace and Low Level Drivers
2023-08-06 Cleaned up PCB
2023-08-07 Cleaned Up Schematic
    Added Blockdiagram
    Reannotated Symbols
2023-08-07 Updated Component Selection
    Better availability
2023-08-07 Updated STM IO Configuration
2023-08-08 Cost calculation
    Find extended parts on mouser
2023-08-08 stm metadata
2023-08-08 Started Board Rev3
    Optimize Component Costs
    Smaller Buck Converter ->
    Move STM32 3mm to the right to simplify SD Card, IMU, TFT routing
2023-08-08 added Datasheets to components
2023-08-08 upd images
2023-08-08 upd board
2023-08-11 upd docs
2023-08-12 Archived Old versions
2023-08-12 FInalised Revision 2 Design
2023-08-12 Gererated Gerber Files
2023-08-12 upd fields
2023-08-13 rm prod_files
    regenerate when needed
2023-08-13 upd board
    Small cleanups
    - better XTAL isolation
    - STM32: lower inductance supply
2023-08-17 upd gitignore
2023-08-17 cleanup
2023-08-17 upd gitignore and README
2023-10-12 updated to R3
2025-05-31 update Revisions and backups
